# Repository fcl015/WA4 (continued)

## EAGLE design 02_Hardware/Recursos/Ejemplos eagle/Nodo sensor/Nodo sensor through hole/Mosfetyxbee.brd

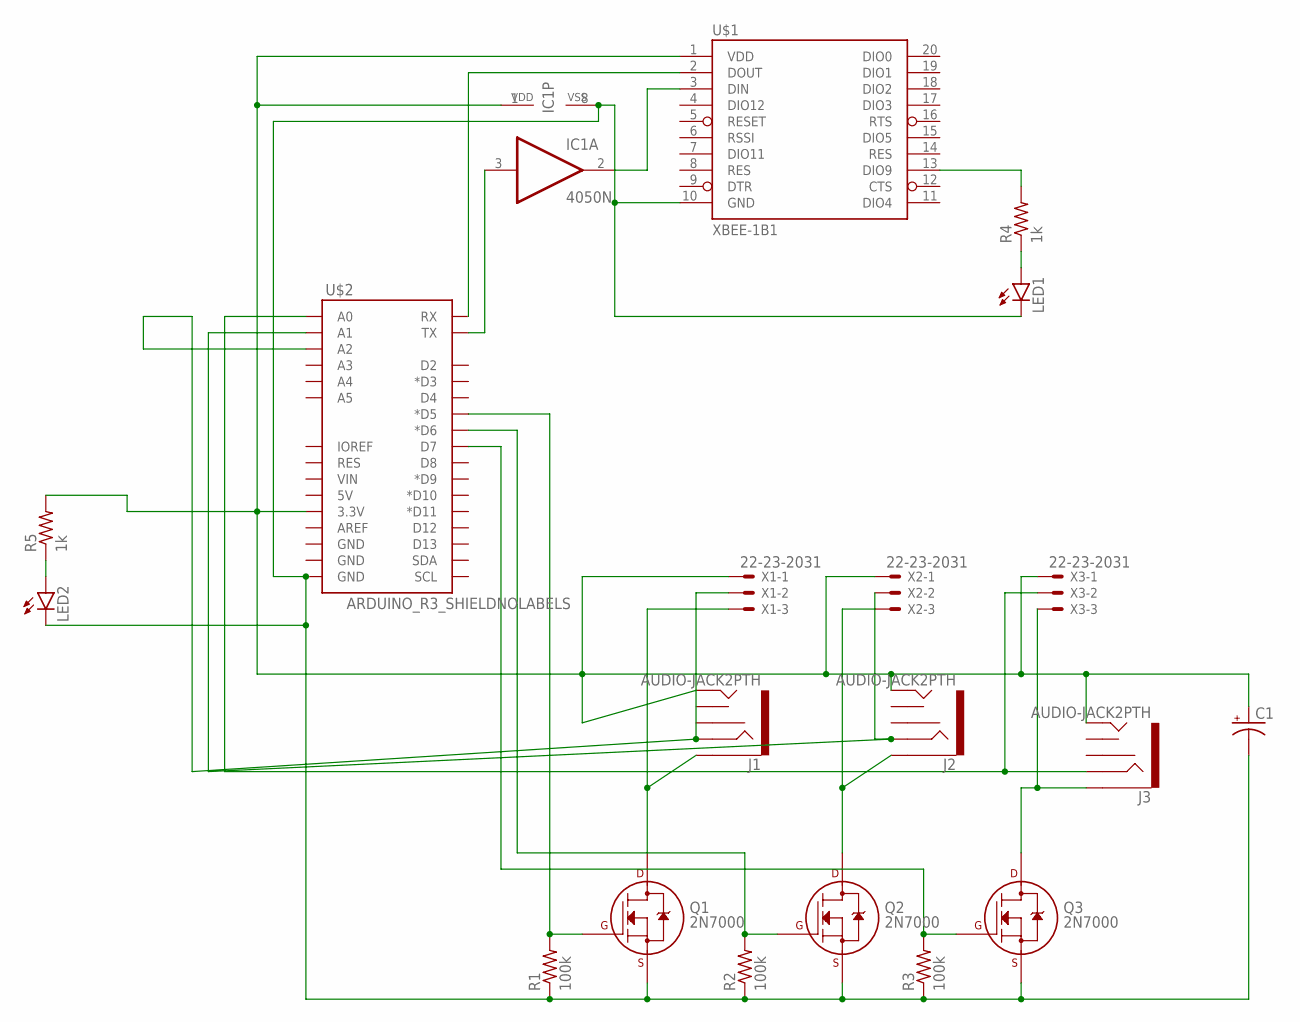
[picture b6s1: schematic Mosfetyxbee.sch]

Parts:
C1: CAP_POLPTH2; CPOL-RADIAL-10UF-25V
IC1: 4050N; DIL16
J1, J2, J3: AUDIO-JACK2PTH; AUDIO-JACK
LED1, LED2: LED3MM
Q1, Q2, Q3: 2N7000; TO-92
R1, R2, R3: 100k; 0207/12
R4, R5: 1k; 0207/10
U$1: XBEE-1B1; XBEE-1
U$2: ARDUINO_R3_SHIELDNOLABELS; UNO_R3_SHIELD_NOLABELS
X1, X2, X3: 22-23-2031

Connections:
unnamed: Q1.2 (G), R1.2, U$2.D5 (*D5)
unnamed: Q2.2 (G), R2.2, U$2.D6 (*D6)
unnamed: Q3.2 (G), R3.2, U$2.D7
unnamed: J1.SLEEVE, Q1.3 (D), X1.3
unnamed: J2.SLEEVE, Q2.3 (D), X2.3
unnamed: J3.SLEEVE, Q3.3 (D), X3.3
unnamed: C1.1 (+), IC1.1 (VDD), J1.TIP, J2.TIP, J3.TIP, R5.2, U$1.1 (VDD), U$2.3.3V, X1.1, X2.1, X3.1
unnamed: C1.2 (-), IC1.8 (VSS), LED1.K (C), LED2.K (C), Q1.1 (S), Q2.1 (S), Q3.1 (S), R1.1, R2.1, R3.1, U$1.10 (GND), U$2.GND@0 (GND)
unnamed: J1.RING, U$2.A2, X1.2
unnamed: J2.RING, U$2.A1, X2.2
unnamed: J3.RING, U$2.A0, X3.2
unnamed: IC1.3 (I), U$2.TX
unnamed: IC1.2 (O), U$1.3 (DIN)
unnamed: U$1.2 (DOUT), U$2.RX
unnamed: R4.2, U$1.13 (DIO9)
unnamed: LED1.A, R4.1
unnamed: LED2.A, R5.1

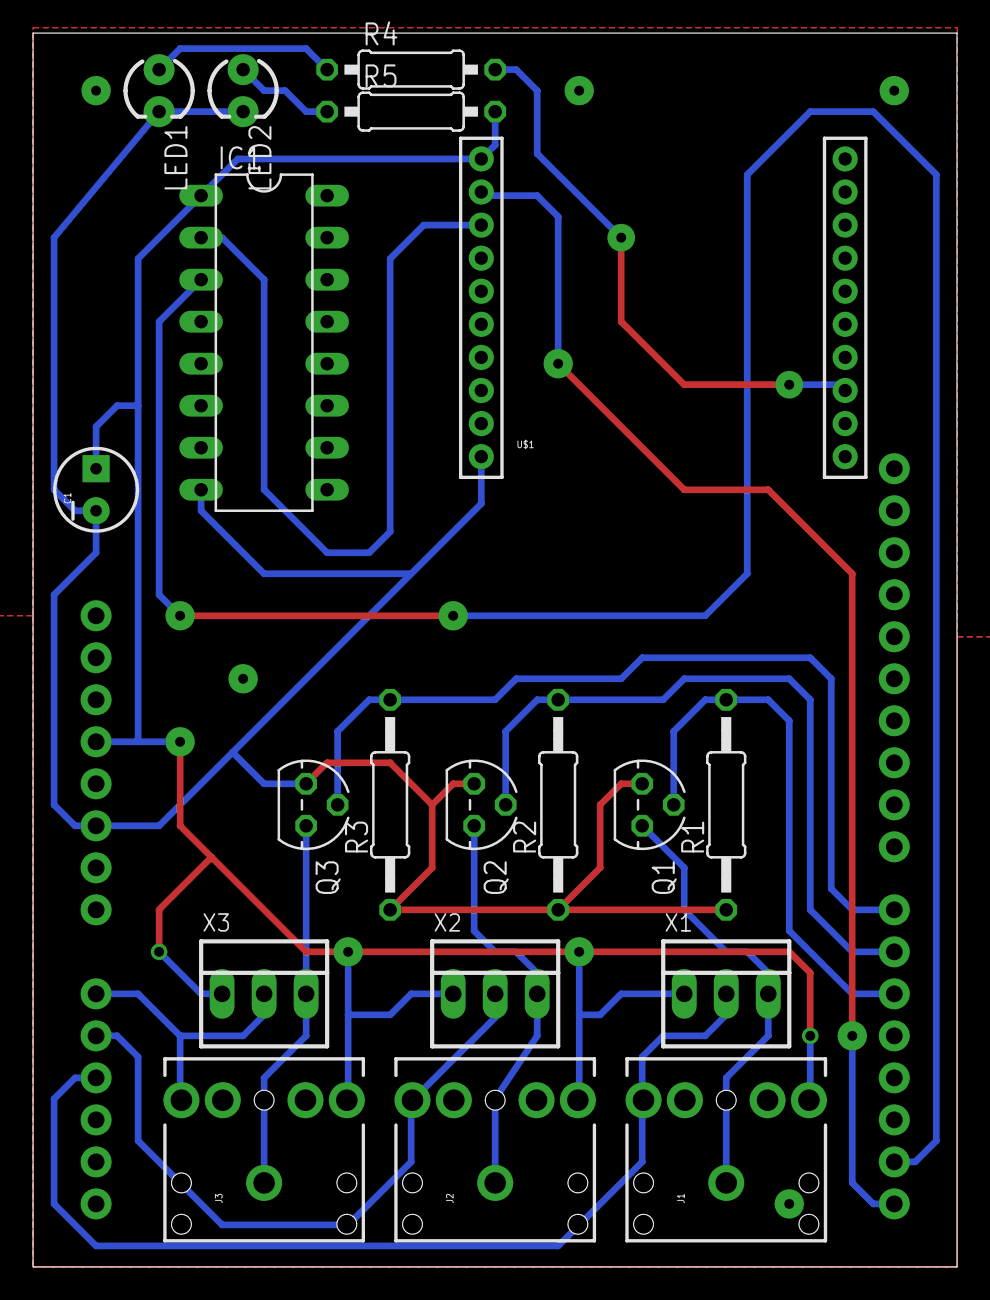
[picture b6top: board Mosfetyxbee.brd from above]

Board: 2 copper layers, 55.9 x 74.6 mm, 20 parts (0 on the bottom side), 17 nets.

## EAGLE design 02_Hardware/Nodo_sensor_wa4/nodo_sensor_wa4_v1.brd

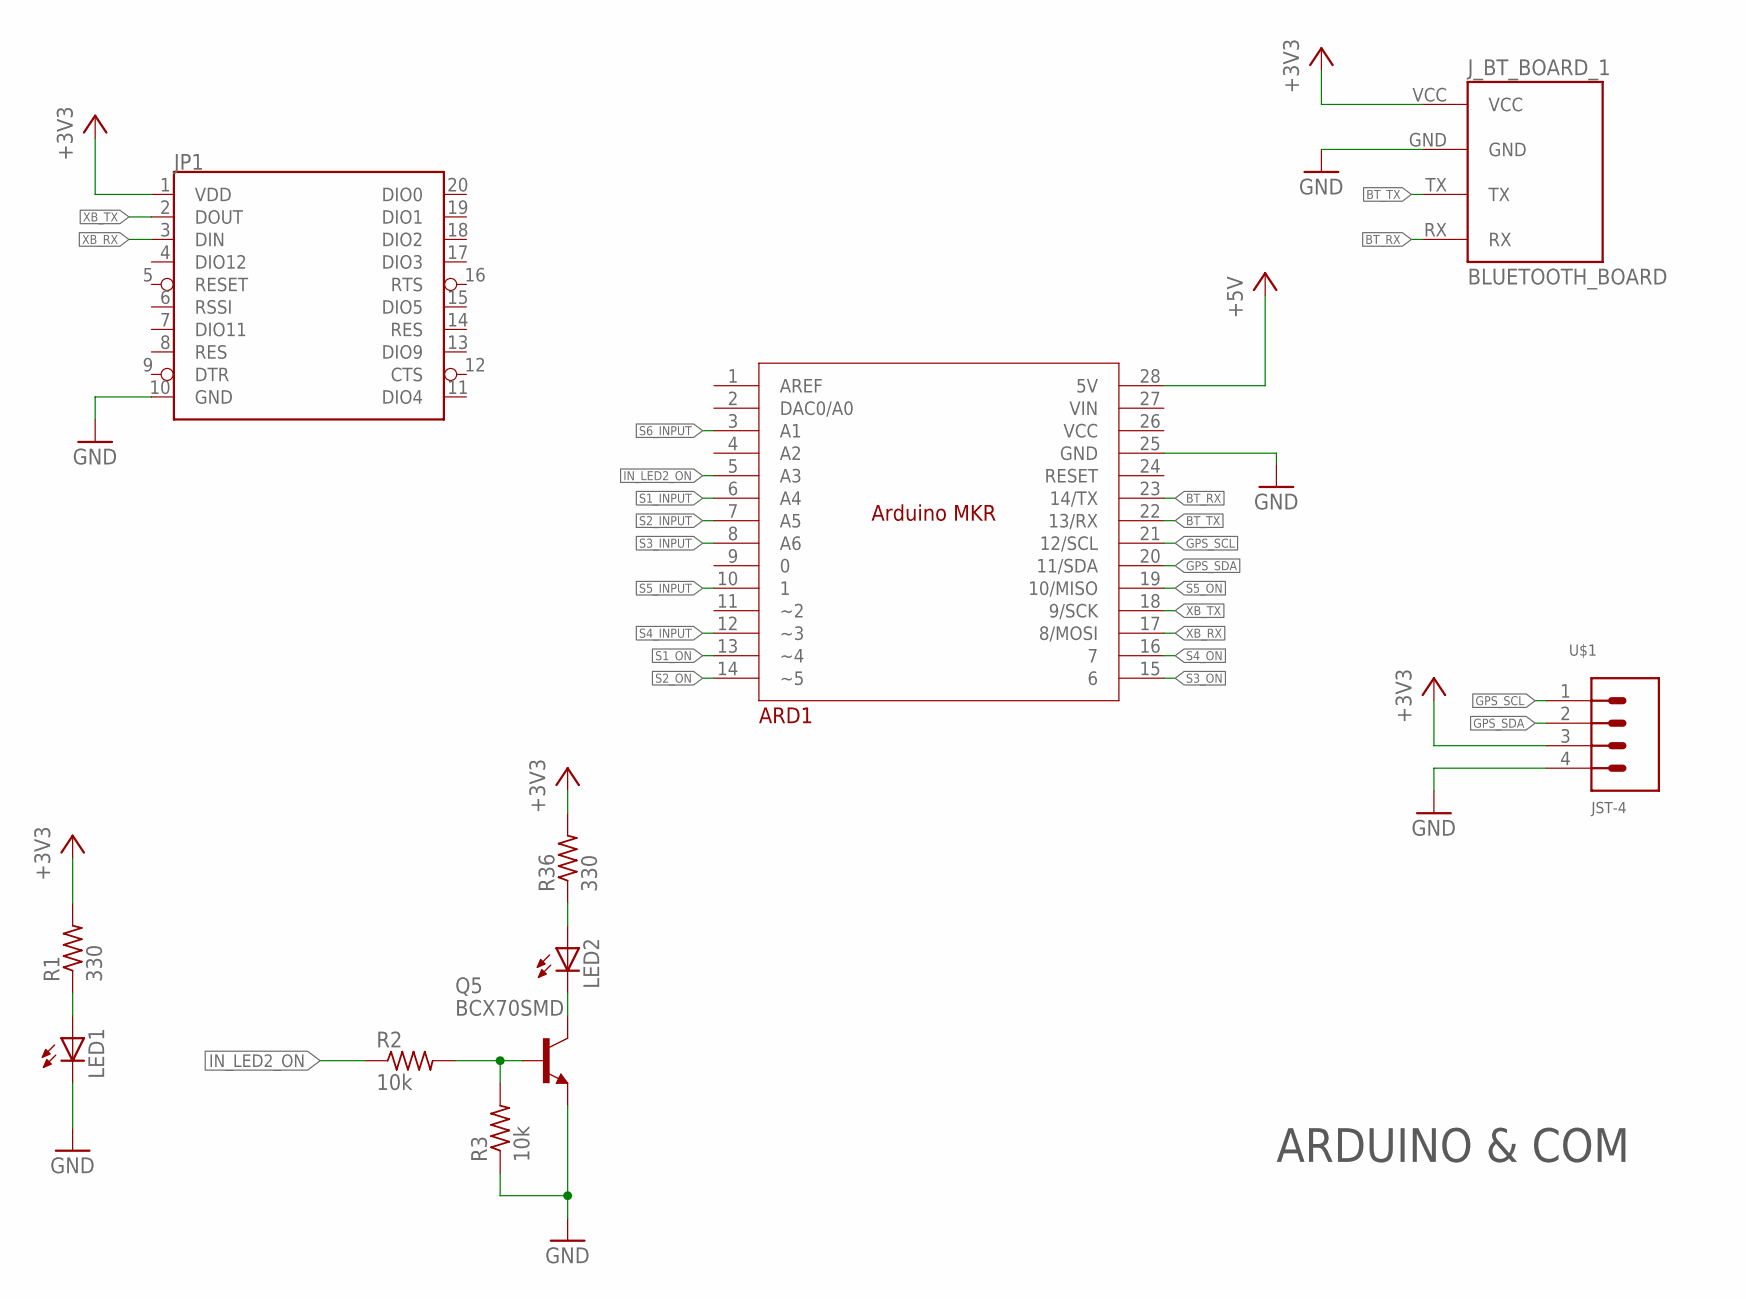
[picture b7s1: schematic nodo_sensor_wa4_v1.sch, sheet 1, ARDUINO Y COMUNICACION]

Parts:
ARD1: ARDUINO_MKR
JP1: XBEE
J_BT_BOARD_1: BLUETOOTH_BOARD; BT_BOARD_FOOTPRINT
LED1, LED2: LEDCHIP-LED0805; CHIP-LED0805
Q5: BCX70SMD; SOT23
R1, R36: 330; R0805
R2, R3: 10k; R0805
U$1: JST-4

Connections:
+3V3: JP1.1 (VDD), J_BT_BOARD_1.VCC, R1.2, R36.2, U$1.3; also elsewhere on the board
+5V: ARD1.28 (5V); also elsewhere on the board
BT_RX: ARD1.23 (14/TX), J_BT_BOARD_1.RX
BT_TX: ARD1.22 (13/RX), J_BT_BOARD_1.TX
GND: ARD1.25 (GND), JP1.10 (GND), J_BT_BOARD_1.GND, LED1.C, Q5.2 (E), R3.1, U$1.4; also elsewhere on the board
GPS_SCL: ARD1.21 (12/SCL), U$1.1
GPS_SDA: ARD1.20 (11/SDA), U$1.2
IN_LED2_ON: ARD1.5 (A3), R2.1
unnamed: LED2.A, R36.1
unnamed: LED2.C, Q5.3 (C)
unnamed: LED1.A, R1.1
unnamed: Q5.1 (B), R2.2, R3.2
S1_INPUT: ARD1.6 (A4); also elsewhere on the board
S1_ON: ARD1.13 (~4); also elsewhere on the board
S2_INPUT: ARD1.7 (A5); also elsewhere on the board
S2_ON: ARD1.14 (~5); also elsewhere on the board
S3_INPUT: ARD1.8 (A6); also elsewhere on the board
S3_ON: ARD1.15 (6); also elsewhere on the board
S4_INPUT: ARD1.12 (~3); also elsewhere on the board
S4_ON: ARD1.16 (7); also elsewhere on the board
S5_INPUT: ARD1.10 (1); also elsewhere on the board
S5_ON: ARD1.19 (10/MISO); also elsewhere on the board
S6_INPUT: ARD1.3 (A1); also elsewhere on the board
XB_RX: ARD1.17 (8/MOSI), JP1.3 (DIN)
XB_TX: ARD1.18 (9/SCK), JP1.2 (DOUT)

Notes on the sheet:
ARDUINO & COM

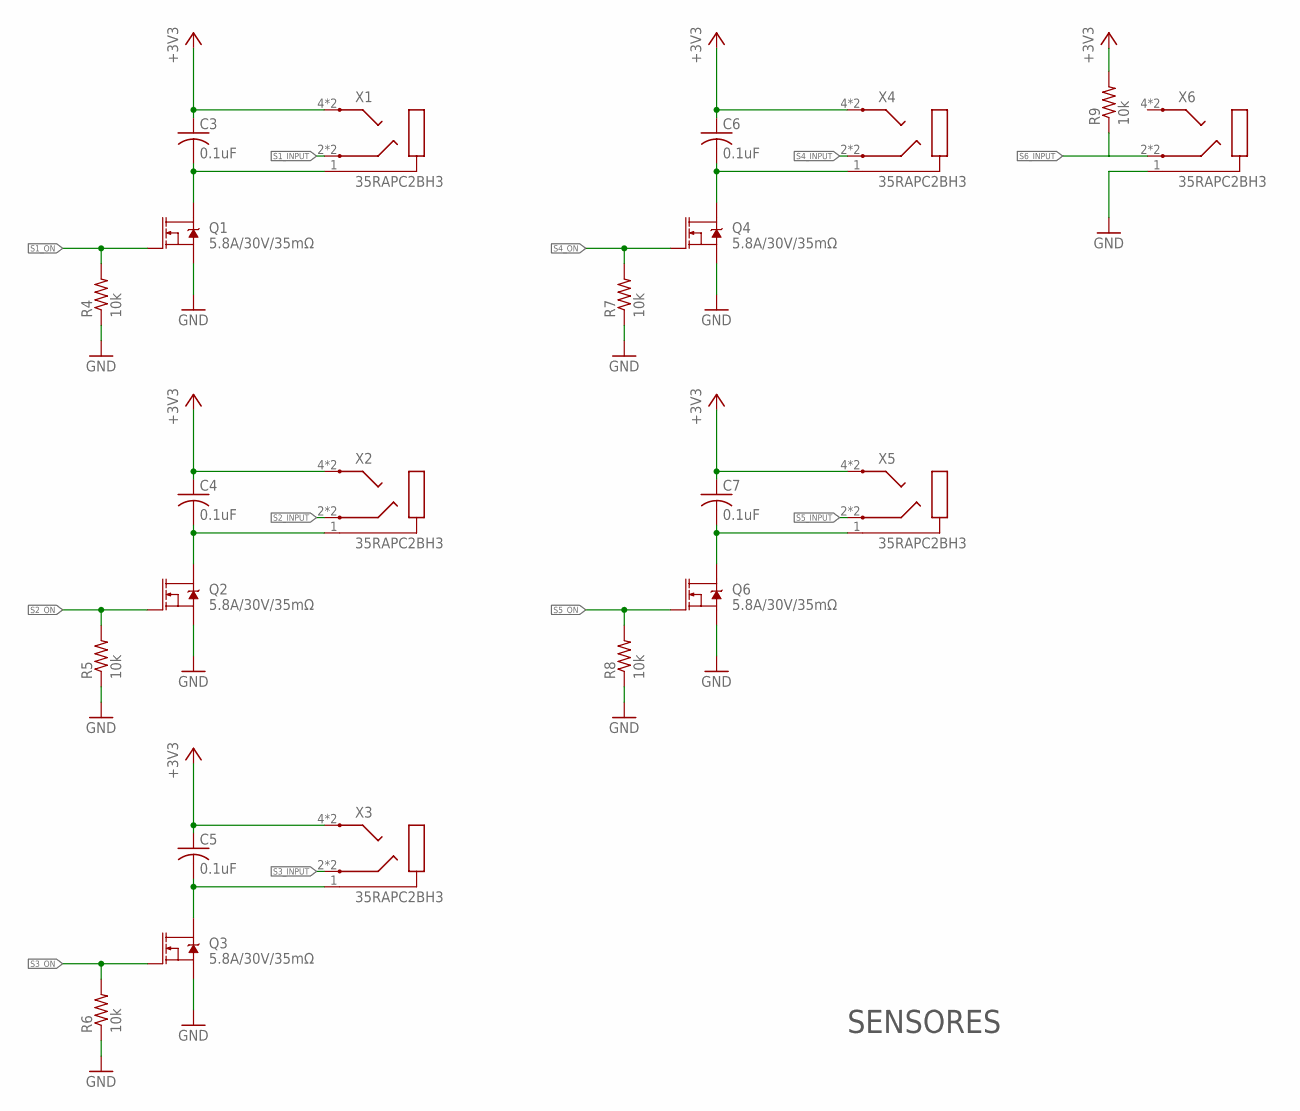
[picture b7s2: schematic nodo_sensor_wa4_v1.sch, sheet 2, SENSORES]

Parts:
C3, C4, C5, C6, C7: 0.1uF; C0805
Q1, Q2, Q3, Q4, Q6: 5.8A/30V/35mΩ; SOT23-3
R4, R5, R6, R7, R8, R9: 10k; R0805
X1, X2, X3, X4, X5, X6: 35RAPC2BH3

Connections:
+3V3: C3.1, C4.1, C5.1, C6.1, C7.1, R9.2, X1.4 (5), X1.5, X2.4 (5), X2.5, X3.4 (5), X3.5, X4.4 (5), X4.5, X5.4 (5), X5.5; also elsewhere on the board
GND: Q1.2 (S), Q2.2 (S), Q3.2 (S), Q4.2 (S), Q6.2 (S), R4.1, R5.1, R6.1, R7.1, R8.1, X6.1; also elsewhere on the board
unnamed: C3.2, Q1.3 (D), X1.1
unnamed: C4.2, Q2.3 (D), X2.1
unnamed: C5.2, Q3.3 (D), X3.1
unnamed: C6.2, Q4.3 (D), X4.1
unnamed: C7.2, Q6.3 (D), X5.1
S1_INPUT: X1.2, X1.3 (2); also elsewhere on the board
S1_ON: Q1.1 (G), R4.2; also elsewhere on the board
S2_INPUT: X2.2, X2.3 (2); also elsewhere on the board
S2_ON: Q2.1 (G), R5.2; also elsewhere on the board
S3_INPUT: X3.2, X3.3 (2); also elsewhere on the board
S3_ON: Q3.1 (G), R6.2; also elsewhere on the board
S4_INPUT: X4.2, X4.3 (2); also elsewhere on the board
S4_ON: Q4.1 (G), R7.2; also elsewhere on the board
S5_INPUT: X5.2, X5.3 (2); also elsewhere on the board
S5_ON: Q6.1 (G), R8.2; also elsewhere on the board
S6_INPUT: R9.1, X6.2, X6.3 (2); also elsewhere on the board

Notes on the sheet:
SENSORES

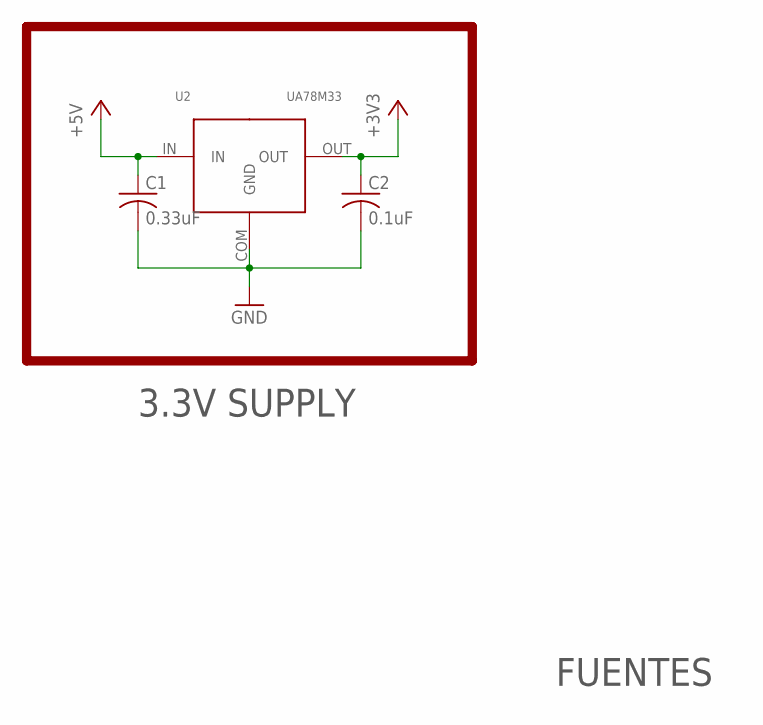
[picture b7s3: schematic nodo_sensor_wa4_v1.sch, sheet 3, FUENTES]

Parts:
C1: 0.33uF; C0805
C2: 0.1uF; C0805
U2: UA78M33; UA78XX

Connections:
+3V3: C2.1, U2.OUT; also elsewhere on the board
+5V: C1.1, U2.IN; also elsewhere on the board
GND: C1.2, C2.2, U2.COM (GND); also elsewhere on the board

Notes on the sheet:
FUENTES
3.3V SUPPLY

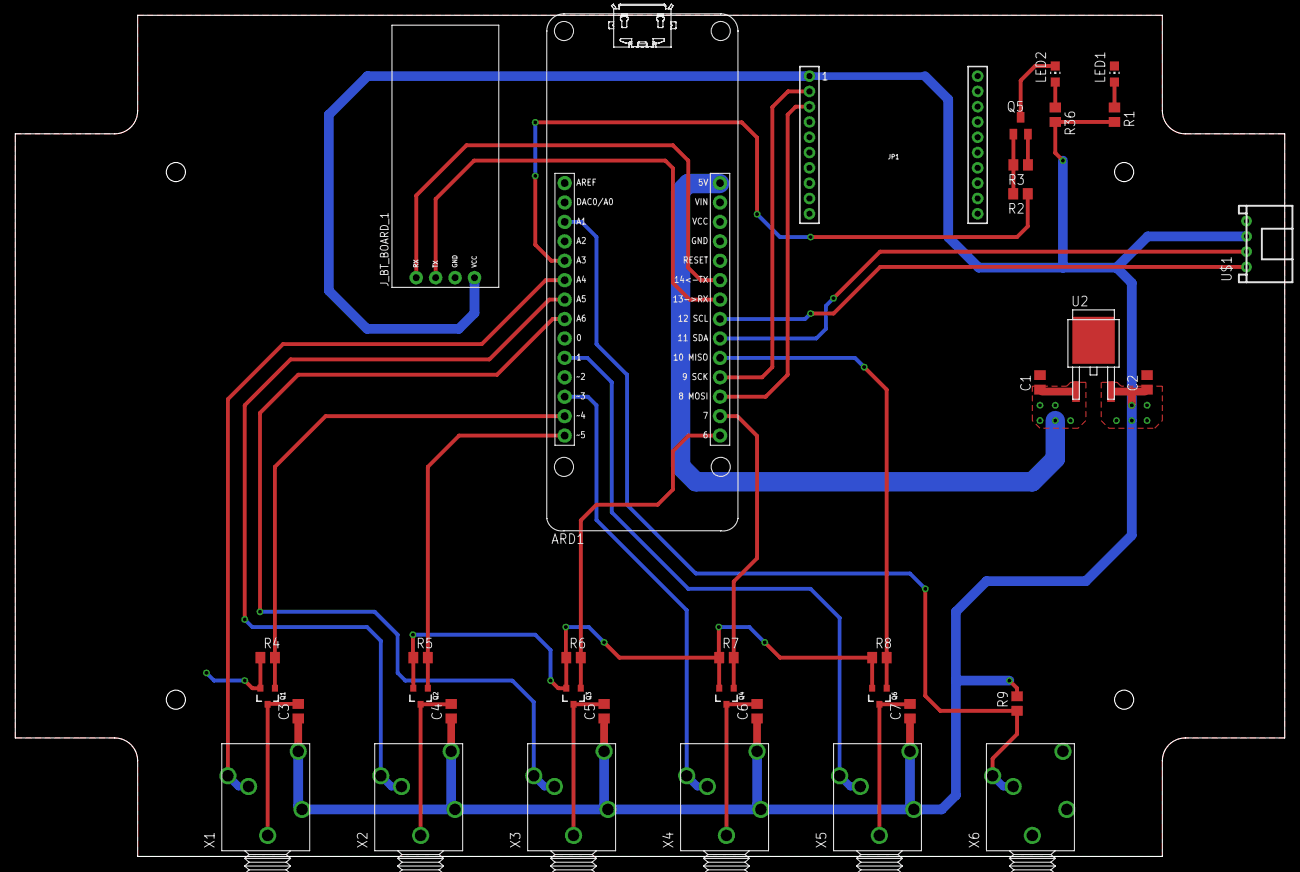
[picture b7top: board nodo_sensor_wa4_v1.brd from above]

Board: 2 copper layers, 166.0 x 110.0 mm, 36 parts (0 on the bottom side), 30 nets.

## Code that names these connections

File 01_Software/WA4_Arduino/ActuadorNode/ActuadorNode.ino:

 
 /*===================================================================================================================================*/
/*=====                                          Sensor node firmware v4.0                                                      =====*/
/*=====                                                   ARDUINO Mega                                                           =====*/
/*=====                                              Water Automation                                                           =====*/
/*=====                                                                                                                         =====*/
/*=====                                                                                                                         =====*/
/*=====                                                                                                                         =====*/
/*===================================================================================================================================*/

/*----------Variables de configuracion-------------*/
int standalone=1; // 1-standalone, 0-Zigbee comm

// Define output locations
#define VALVE1_ON   digitalWrite(7, HIGH)
#define VALVE1_OFF  digitalWrite(7, LOW)
#define VALVE2_ON   digitalWrite(6, HIGH)
#define VALVE2_OFF  digitalWrite(6, LOW)
#define VALVE3_ON   digitalWrite(5, HIGH)
#define VALVE3_OFF  digitalWrite(5, LOW)
#define LED1_ON     digitalWrite(9, HIGH)
#define LED1_OFF    digitalWrite(9, LOW)
#define LED2_ON     digitalWrite(10, HIGH)
#define LED2_OFF    digitalWrite(10, LOW)
#define LED3_ON     digitalWrite(11, HIGH)
#define LED3_OFF    digitalWrite(11, LOW)
  
// declare global variables
 char bufferin[80];
 unsigned char buffout[80];
 char serial_cmd[10];
 char valve1_status;
 char valve2_status;
 char valve3_status;

 unsigned char battery_level = 0xFF;
 unsigned char pressure_units = 0x42;
 int sum;
 unsigned char pressure_decimals = 0x42;
 float discharge2 =0;
 float discharge =0;


 unsigned long tiempoanterior;
 unsigned long tiempo=60000; //time for discharge calc
 unsigned long flow_counter = 0;
 int i = 0;
 
char input_message_size=22;
char output_message_size=32;

//---------------------------------------------------------
// Set-up function
//--------------------------------------------------------- 
void setup(){
 
   pinMode(9, OUTPUT); //LED 1
   pinMode(10, OUTPUT);//LED 2
   pinMode(11, OUTPUT);//LED 3
   pinMode(6, OUTPUT); //VALVE 2
   pinMode(7, OUTPUT); //VALVE 1
   pinMode(5, OUTPUT); //VALVE 3
   attachInterrupt(0, flow, RISING);
   Serial.begin(9600);

   for(int j=0; j<255 ; j++) {analogWrite(9,j); delay(2);}
   for(int j=255; j>=0 ; j--) {analogWrite(9,j); delay(2);}
   for(int j=0; j<255 ; j++) {analogWrite(10,j); delay(2);}
   for(int j=255; j>=0 ; j--) {analogWrite(10,j); delay(2);}
   for(int j=0; j<255 ; j++) {analogWrite(11,j); delay(2);}
   for(int j=255; j>=0 ; j--) {analogWrite(11,j); delay(2);}
   
  digitalWrite(7, HIGH);
  digitalWrite(9, HIGH);
  delay(300);
  digitalWrite(7, LOW);
  digitalWrite(9, LOW);
  delay(300);
  digitalWrite(6, HIGH);
  digitalWrite(10, HIGH);
  delay(300);
  digitalWrite(6, LOW);
  digitalWrite(10, LOW);
  delay(300);
  digitalWrite(5, HIGH);
  digitalWrite(11, HIGH);
  delay(300);
  digitalWrite(5, LOW);
  digitalWrite(11, LOW);
  delay(300);
 }
 
//---------------------------------------------------------
// Main loop
//---------------------------------------------------------
void loop(){
  
 if(valve1_status == 1) LED1_ON;
 else LED1_OFF;
 
 if(valve2_status == 1) LED2_ON;
 else LED2_OFF;
 
 if(valve3_status == 1) LED3_ON;
 else LED3_OFF;

 unsigned long tiempoactual=millis();
  
 if(tiempoactual - tiempoanterior > tiempo) {         
          discharge_calc(flow_counter);  
          if( standalone==1){
              Serial.println("-------------");
              Serial.println("FLOW SENSOR");
              Serial.println("-------------");
              Serial.print("Flow Counter: ");
              Serial.println(flow_counter,DEC);
              Serial.print("Discharge: ");
              Serial.println(discharge,2);
              Serial.print("Discharge2: ");
              Serial.println(discharge2,2);
           }
          flow_counter = 0;
          tiempoanterior = tiempoactual; 
 }
}
 
//---------------------------------------------------------
// Process Xbee message and send a response
//---------------------------------------------------------
void serialEvent(){
  char serial_cmd[11];
  i = 0;
  if( standalone==0){
    if(Serial.available()>0){  
      Serial.readBytes(bufferin,input_message_size);
      if(bufferin[0] == 0x7E && bufferin[15]== 'A'){
          if(bufferin[16] == '1') {valve1_status = 1; VALVE1_ON; }
          else if(bufferin[16] == '0'){valve1_status = 0; VALVE1_OFF;}
          if(bufferin[17] == '1') {valve2_status = 1; VALVE2_ON; }
          else if(bufferin[17] == '0'){valve2_status = 0; VALVE2_OFF;}
          if(bufferin[18] == '1') {valve3_status = 1; VALVE3_ON; }
          else if(bufferin[18] == '0'){valve3_status = 0; VALVE3_OFF;}
           
          buffout[0]=0x7E;//API mode start delimeter
          buffout[1]=0x00;//Data length MSB
          buffout[2]=output_message_size-4;//Data length LSB
          buffout[3]=0x10;//API ID TX Request 16 bit address
          buffout[4]=0x00;//Frame ID, if equals to 0x00 disable response frame
          buffout[5]=bufferin[4];
          buffout[6]=bufferin[5];
          buffout[7]=bufferin[6];
          buffout[8]=bufferin[7];
          buffout[9]=bufferin[8];
          buffout[10]=bufferin[9];
          buffout[11]=bufferin[10];
          buffout[12]=bufferin[11];//Destination Address LSB
          buffout[13]=0xFF;
          buffout[14]=0xFE;
          buffout[15]=0x00;
          buffout[16]=0x00;
          buffout[17]='A'; 
          buffout[18]=valve1_status;
          buffout[19]=valve2_status;
          buffout[20]=valve3_status;
          buffout[21]=highByte((unsigned int)(discharge*100));  //Water Flow liters/minute 
          buffout[22]=lowByte((unsigned int)(discharge*100));  //Water Flow liters/minute 
          buffout[23]=0x00;
          buffout[24]=0x00;
          buffout[25]=0x00;
          buffout[26]=0x00;
          buffout[27]=0x00;
          buffout[28]=0x00;
          buffout[29]=0x00;
          buffout[30]=0x0A;//End of package
          for(int i=3;i<output_message_size-1;i++){
               sum+=buffout[i]; //Checksum
          }
          buffout[31]=0xFF-lowByte(sum);
          sum=0;
          Serial.write(buffout,output_message_size);      
       }
    }
 }
 else{
      char v1,v2,v3;
      v1=Serial.read();
      delay(100);
      v2=Serial.read();
      delay(100);
      v3=Serial.read();
      delay(100);
      if(v1 == '1') {valve1_status = 1; VALVE1_ON; }
      else if(v1 == '0'){valve1_status = 0; VALVE1_OFF;}
      if(v2 == '1') {valve2_status = 1; VALVE2_ON; }
      else if(v2 == '0'){valve2_status = 0; VALVE2_OFF;}
      if(v3 == '1') {valve3_status = 1; VALVE3_ON; }
      else if(v3 == '0'){valve3_status = 0; VALVE3_OFF;}
      Serial.println("-------------");
      Serial.println("ACTUATOR NODE");
      Serial.println("-------------");
      Serial.print("Valve 1: ");
      Serial.println(valve1_status,DEC);
      Serial.print("Valve 2: ");
      Serial.println(valve2_status,DEC);
      Serial.print("Valve 3: ");
      Serial.println(valve3_status,DEC);
  }
}
 
//---------------------------------------------------------
// Count pulses from flow sensor
//---------------------------------------------------------
void flow(){
   digitalWrite(11, HIGH);
   delay(20);
   flow_counter++;
   digitalWrite(11, LOW);
}
 

//---------------------------------------------------------
// Calculate water consumption from pulses
//---------------------------------------------------------
void discharge_calc(unsigned long pulses){
  
  #define offset 0.39
  #define K 0.44
  #define fact_litres 3.78541
 
  if (pulses > 10){
      // Liters = 0.0407*pulses +2.7478 
      discharge = (0.0407*pulses) + 2.7478;// Linear approximation formula
      //Datasheet formula
      discharge2 = (((float)pulses/60) + offset)*K;  // in gallons per minute
      discharge2 = discharge2*fact_litres;
      // 530 pulses = 20 lts = 5.28344 gallons
      //1003 pulses = 10 gallons
  }
  else{
      discharge = 0;  
      discharge2 = 0;
  }  
}

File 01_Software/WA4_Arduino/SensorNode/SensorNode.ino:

/*===================================================================================================================================*/
/*=====                                          Sensor node firmware v4.0                                                      =====*/
/*=====                                                   ARDUINO UNO                                                           =====*/
/*=====                                              Water Automation                                                           =====*/
/*=====                                                                                                                         =====*/
/*=====     To power sensors use digital pins 5, 6 and 7                                                                        =====*/
/*=====     To read sensors use analog pins A0, A1, A2                                                                          =====*/
/*=====                                                                                                                         =====*/
/*=====                                                                                                                         =====*/
/*===================================================================================================================================*/

/*----------Variables de configuracion-------------*/
int standalone=0; // 1-standalone, 0-Zigbee comm
unsigned long timeInterval = 10000;

/*=====Sensor variables=====*/
int S1_ON = 7, S2_ON = 6, S3_ON = 5;
int S1_PORT = A0, S2_PORT = A1, S3_PORT = A2;
int S1_RAW, S2_RAW, S3_RAW;
float S1_MOIST, S2_MOIST, S3_MOIST;
char soil_moisture_equation='1';
/*==========================*/

/*=====Communication variables=====*/
char input_message_size=22;
char output_message_size=32;
unsigned char Buffout[80]; 
char Buffin[80];
char XBeeAdd[8] = {0x00, 0x00, 0x00, 0x00, 0x00, 0x00, 0x00, 0x00};
/*=================================*/

/*=====Timer variables=====*/
unsigned long previousMillis;
/*=========================*/

/*=====Misc variables=====*/
char ERRORCODE = 0x00;
char BATLVL = 100;
char NODE_TYPE = 'S';
/*========================*/

int sum1;

//---------------------------------------------------------
// Set-up function
//---------------------------------------------------------
void setup(){
  Serial.begin(9600);
  pinMode(S1_ON, OUTPUT);
  pinMode(S2_ON, OUTPUT);
  pinMode(S3_ON, OUTPUT);
  analogReference(INTERNAL);      // Only for Arduino Uno
  //analogReference(INTERNAL1V1); //Only for Arduino Mega
}


//---------------------------------------------------------
// Process Xbee message and send a response
//---------------------------------------------------------
void serialEvent(){

if( standalone==0){
   if(Serial.available()>0){   
      Serial.readBytes(Buffin,input_message_size);
      if(Buffin[0] == 0x7E && Buffin[15] == 'S'){ 
            soil_moisture_equation=Buffin[16];     
          /*=======Emisor MAC address=======*/
            XBeeAdd[0] = Buffin[4];
            XBeeAdd[1] = Buffin[5];
            XBeeAdd[2] = Buffin[6];
            XBeeAdd[3] = Buffin[7];
            XBeeAdd[4] = Buffin[8];
            XBeeAdd[5] = Buffin[9];
            XBeeAdd[6] = Buffin[10];
            XBeeAdd[7] = Buffin[11];
            /*=================================*/
            /*=======API Frame=======*/
            Buffout[0]=0x7E;                 //API mode start delimeter
            Buffout[1]=0x00;                 //Data length MSB
            Buffout[2]=output_message_size-4;//Data length LSB
            Buffout[3]=0x10;            //API ID TX Request 64 bit address
            Buffout[4]=0x00;            //Frame ID, if equals to 0x00 disable response frame
            Buffout[5]=XBeeAdd[0];      //Destination Address MSB
            Buffout[6]=XBeeAdd[1];            
            Buffout[7]=XBeeAdd[2];
            Buffout[8]=XBeeAdd[3];
            Buffout[9]=XBeeAdd[4];
            Buffout[10]=XBeeAdd[5];
            Buffout[11]=XBeeAdd[6];
            Buffout[12]=XBeeAdd[7];     //Destination Address LSB                
        		Buffout[13]=0xFF;
        		Buffout[14]=0xFE;
        		Buffout[15]=0x00;
        		Buffout[16]=0x00;
            Buffout[17]=NODE_TYPE;           // Node 'S'
            Buffout[18]=highByte(int(S1_MOIST*100)); //SM1 high byte
            Buffout[19]=lowByte(int(S1_MOIST*100));  //SM1 low byte 
            Buffout[20]=highByte(int(S2_MOIST*100)); //SM2 high byte
            Buffout[21]=lowByte(int(S2_MOIST*100));  //SM2 low byte
            Buffout[22]=highByte(int(S3_MOIST*100)); //SM3 high byte
            Buffout[23]=lowByte(int(S3_MOIST*100));  //SM3 low byte
            Buffout[24]=0x00;           //Not used
            Buffout[25]=0x00;           //Not used
            Buffout[26]=0x00;           //Not used
            Buffout[27]=0x00;           //Not used
            Buffout[28]=0x00;           //Not used
            Buffout[29]=0x00;           //Not used
            Buffout[30]=0x0A;           //End of packet
            for(int i=3;i<output_message_size-1;i++){      
                  sum1+=Buffout[i]; //Checksum
            }
            Buffout[31]=0xFF-lowByte(sum1);
            sum1=0;
            Serial.write(Buffout,output_message_size);
      }
   }
 }
}


//---------------------------------------------------------
// Main loop
//---------------------------------------------------------
void loop(){ 
   unsigned long currentMillis = millis();
 
    if(currentMillis - previousMillis > timeInterval) {
        previousMillis = currentMillis;   
        S1_RAW = SensorRead(S1_ON, S1_PORT, 100);
        S2_RAW = SensorRead(S2_ON, S2_PORT, 100);
        S3_RAW = SensorRead(S3_ON, S3_PORT, 100);
    
        S1_MOIST = MoistureCalculation(S1_RAW, soil_moisture_equation, 10, 1.1);
        S2_MOIST = MoistureCalculation(S2_RAW, soil_moisture_equation, 10, 1.1);
        S3_MOIST = MoistureCalculation(S3_RAW, soil_moisture_equation, 10, 1.1);

        // Monitoreo de datos
        if( standalone==1){
                Serial.println("-------------");
                Serial.println("SENSOR NODE");
                Serial.println("-------------");
                Serial.print("SM1 (Raw): ");
                Serial.println(S1_RAW);
                Serial.print("SM1 (VWC): ");
                Serial.println(S1_MOIST);
                Serial.print("SM2 (Raw): ");
                Serial.println(S2_RAW);
                Serial.print("SM2 (VWC): ");
                Serial.println(S2_MOIST);
                Serial.print("SM3 (Raw): ");
                Serial.println(S3_RAW);
                Serial.print("SM3 (VWC): ");
                Serial.println(S3_MOIST);
          }
    }
}

//---------------------------------------------------------
// Read soil moisture analog values
//---------------------------------------------------------
int SensorRead(int port_ON, int port_adc, int stab_time){
  int rawData;

  digitalWrite(port_ON, HIGH);
  delay(stab_time);
  rawData = analogRead(port_adc);
  delay(20);
  digitalWrite(port_ON, LOW);
  delay(20);
  
  return rawData;
}


//---------------------------------------------------------
// Calculate soil moisture from sensor reading
//---------------------------------------------------------
float MoistureCalculation(int SensorRaw, char eq_num, int adc_resolution, float voltage_reference){
    float moisture;
    float milivolts;
    float milivolts_resolution;
    
    milivolts_resolution = float((voltage_reference/(pow(2,adc_resolution) - 1))*1000);
    milivolts = float(SensorRaw * milivolts_resolution);
       
    switch(eq_num){
        case '0':     /* Factory Calibration */
        moisture = ((0.00119*milivolts) - 0.4000)*100;  
        break;
        
        case '1':     /* Area TEC EC5 */
        moisture = ((0.0009*milivolts) - 0.3487)*100;  
        break;
        
        case '2':     /* Area TEC 10HS */
        moisture = ((0.0008*milivolts) - 0.4138)*100;
        break;
        
        case '3':     /* Area Delicias EC5 */
        moisture = ((0.0009*milivolts) - 0.3926)*100;  
        break;
        
        case '4':     /* Area Delicias 10HS */
        moisture = ((0.0008*milivolts) - 0.4897)*100;
        break;
        
        case '5':     /* Area GranjaHogar EC5 */
        moisture = ((0.0009*milivolts) - 0.3487)*100;  
        break;
        
        case '6':     /* Area GranjaHogar 10HS */
        moisture = ((0.0008*milivolts) - 0.3681)*100;
        break;

        default:     /* Factory Calibration */
        moisture = ((0.00119*milivolts) - 0.4000)*100;  
        break;
    }
    if (moisture < 0.0) {
        moisture=0.0;      
        }
        
    return moisture;
}

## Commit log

2020-03-10 Initial import
